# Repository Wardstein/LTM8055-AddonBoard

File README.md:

# LTM8055 Addon Board

This is a small 4 layer addon board with an [LTM8055(-1) DCDC regulator](https://www.analog.com/en/products/ltm8055.html), featuring an INA138 for output current measurement (as the internal current monitor output of the LTM8055 is not very accurate). Additionally a lot of the LTM8055 configuration pins are broken out to a header to be used on the base-board. But this small addon board can also be used as a standalone board, just fit the voltage feedback resistors on this board.

The LTM8055 is a 5-36V input, 8,5A Buck-Boost μModule Regulator with step-up and -down capability from 1,2V to 36V output.

Why use an addon board? This was developed, as the LTM8055 µModules are BGA parts, which are not the easiest parts for home use and soldering. This module can be very easily be soldered on a hotplate (I use the Miniware MHP30).

This board is for example used in the [joseng.de Lab-Box project](https://github.com/Wardstein/Lab-Box) in the multi-power-supply module. 

# License
The content of this whole repository is licensed under [CERN-OHL-W v2](License/cern_ohl_w_v2.txt) or later by Jonas Eberhard.

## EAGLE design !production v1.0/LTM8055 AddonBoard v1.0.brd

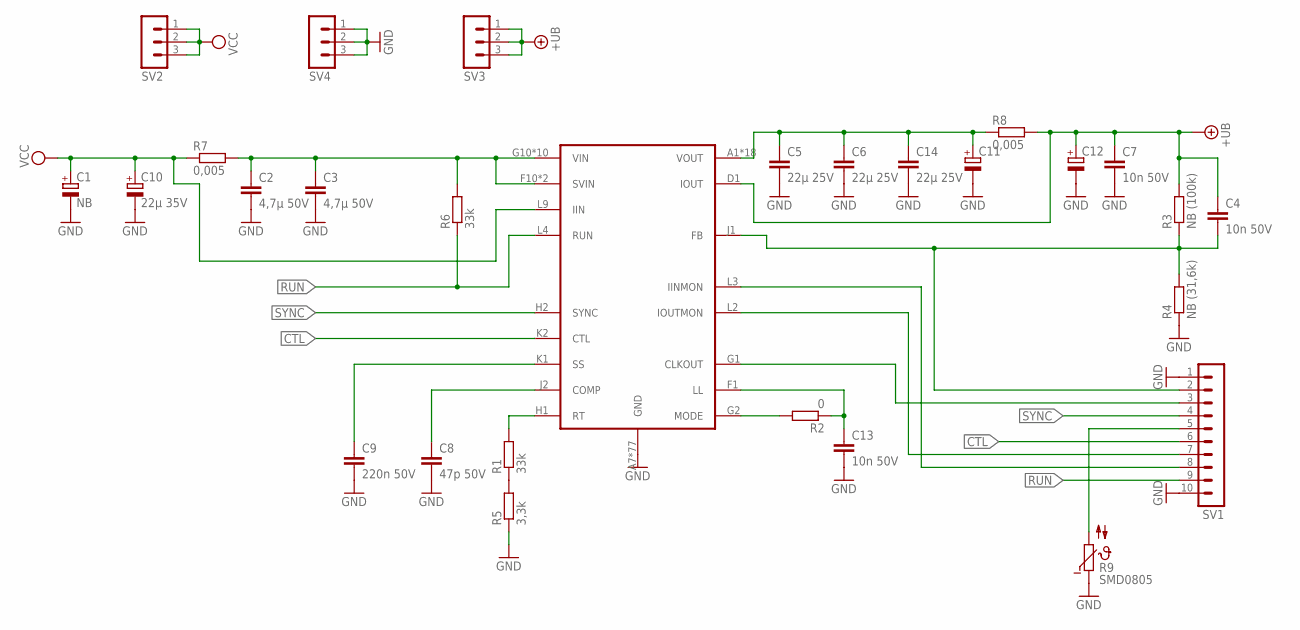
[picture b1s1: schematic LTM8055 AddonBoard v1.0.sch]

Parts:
C1: NB; PANASONIC_E
C2, C3: 4,7µ 50V; C1206
C4, C7, C13: 10n 50V; C0805
C5, C6, C14: 22µ 25V; C1210
C8: 47p 50V; C0805
C9: 220n 50V; C0805
C10: 22µ 35V; D/7343-31R
C11, C12: CPOL-EUD/7343-31R; D/7343-31R
IC1: LTM8055-1; BGA121_1.27_15X15MM
R1, R6: 33k; R0805
R2: 0; R0805
R3: NB (100k); R0805
R4: NB (31,6k); R0805
R5: 3,3k; R0805
R7, R8: 0,005; R2512
R9: SMD0805; R0805
SV1: MA10-1
SV2, SV3, SV4: MA03-1

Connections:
+UB: C4.1, C7.1, C12.+, IC1.D1 (IOUT), R3.2, R8.2, SV3.1, SV3.2, SV3.3
CTL: IC1.K2 (CTL), SV1.6
GND: C1.-, C2.2, C3.2, C5.2, C6.2, C7.2, C8.2, C9.2, C10.-, C11.-, C12.-, C13.2, C14.2, IC1.A7 (GND), IC1.A8 (GND), IC1.A9 (GND), IC1.A10 (GND), IC1.A11 (GND), IC1.B7 (GND), IC1.B8 (GND), IC1.B9 (GND), IC1.B10 (GND), IC1.B11 (GND), IC1.C7 (GND), IC1.C8 (GND), IC1.C9 (GND), IC1.C10 (GND), IC1.C11 (GND), IC1.D2 (GND), IC1.D3 (GND), IC1.D4 (GND), IC1.D5 (GND), IC1.D6 (GND), IC1.D7 (GND), IC1.D8 (GND), IC1.D9 (GND), IC1.D10 (GND), IC1.D11 (GND), IC1.E1 (GND), IC1.E2 (GND), IC1.E3 (GND), IC1.E4 (GND), IC1.E5 (GND), IC1.E6 (GND), IC1.E7 (GND), IC1.E8 (GND), IC1.E9 (GND), IC1.E10 (GND), IC1.E11 (GND), IC1.F2 (GND), IC1.F3 (GND), IC1.F4 (GND), IC1.F5 (GND), IC1.F6 (GND), IC1.F7 (GND), IC1.F8 (GND), IC1.F9 (GND), IC1.G3 (GND), IC1.G4 (GND), IC1.G5 (GND), IC1.G6 (GND), IC1.G7 (GND), IC1.G8 (GND), IC1.G9 (GND), IC1.H3 (GND), IC1.H4 (GND), IC1.H5 (GND), IC1.H6 (GND), IC1.H7 (GND), IC1.H8 (GND), IC1.H9 (GND), IC1.J3 (GND), IC1.J4 (GND), IC1.J5 (GND), IC1.J6 (GND), IC1.J7 (GND), IC1.J8 (GND), IC1.J9 (GND), IC1.K3 (GND), IC1.K4 (GND), IC1.K5 (GND), IC1.K6 (GND), IC1.K7 (GND), IC1.K8 (GND), IC1.K9 (GND), IC1.L1 (GND), IC1.L5 (GND), IC1.L6 (GND), IC1.L7 (GND), IC1.L8 (GND), R4.1, R5.1, R9.1, SV1.1, SV1.10, SV4.1, SV4.2, SV4.3
unnamed: C13.1, IC1.F1 (LL), R2.1
unnamed: IC1.G2 (MODE), R2.2
unnamed: IC1.G1 (CLKOUT), SV1.3
unnamed: C9.1, IC1.K1 (SS)
unnamed: C4.2, IC1.J1 (FB), R3.1, R4.2, SV1.2
unnamed: IC1.L2 (IOUTMON), SV1.7
unnamed: IC1.L3 (IINMON), SV1.8
unnamed: IC1.H1 (RT), R1.2
unnamed: C2.1, C3.1, IC1.F10 (SVIN), IC1.F11 (SVIN), IC1.G10 (VIN), IC1.G11 (VIN), IC1.H10 (VIN), IC1.H11 (VIN), IC1.J10 (VIN), IC1.J11 (VIN), IC1.K10 (VIN), IC1.K11 (VIN), IC1.L10 (VIN), IC1.L11 (VIN), R6.2, R7.2
unnamed: R1.1, R5.2
unnamed: C8.1, IC1.J2 (COMP)
unnamed: R9.2, SV1.5
unnamed: C5.1, C6.1, C11.+, C14.1, IC1.A1 (VOUT), IC1.A2 (VOUT), IC1.A3 (VOUT), IC1.A4 (VOUT), IC1.A5 (VOUT), IC1.A6 (VOUT), IC1.B1 (VOUT), IC1.B2 (VOUT), IC1.B3 (VOUT), IC1.B4 (VOUT), IC1.B5 (VOUT), IC1.B6 (VOUT), IC1.C1 (VOUT), IC1.C2 (VOUT), IC1.C3 (VOUT), IC1.C4 (VOUT), IC1.C5 (VOUT), IC1.C6 (VOUT), R8.1
RUN: IC1.L4 (RUN), R6.1, SV1.9
SYNC: IC1.H2 (SYNC), SV1.4
VCC: C1.+, C10.+, IC1.L9 (IIN), R7.1, SV2.1, SV2.2, SV2.3

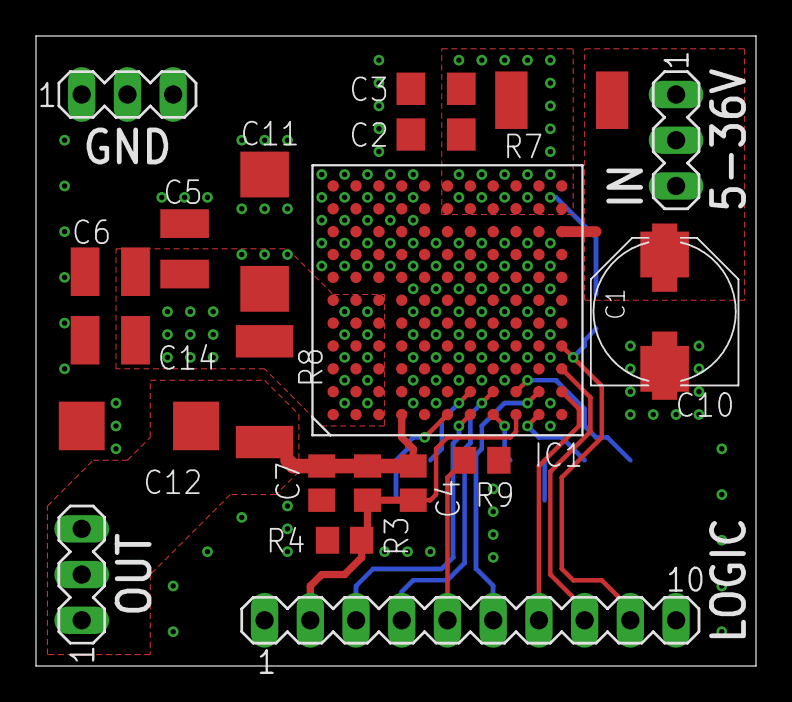
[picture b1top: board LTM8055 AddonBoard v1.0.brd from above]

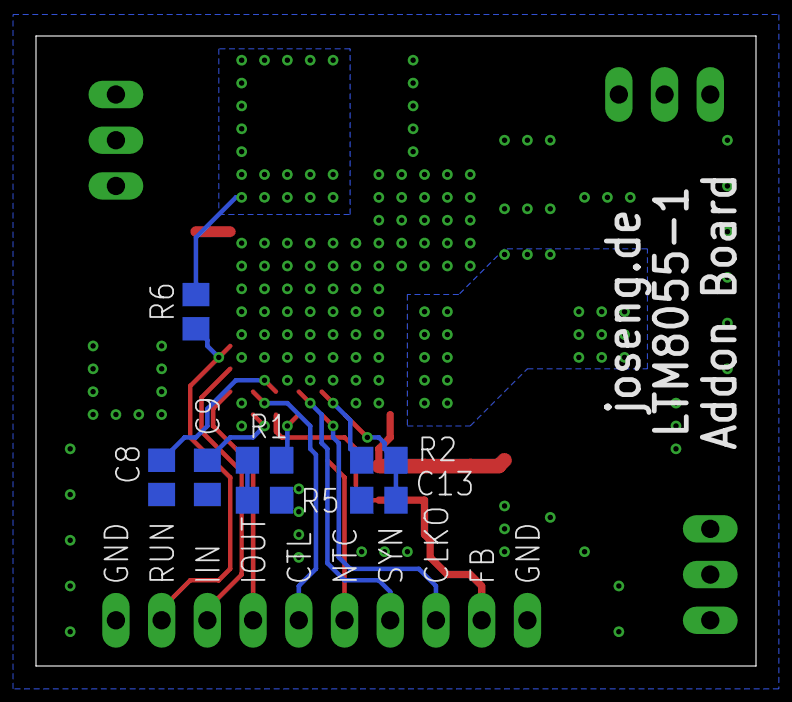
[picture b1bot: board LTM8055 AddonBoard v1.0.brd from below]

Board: 4 copper layers, 40.0 x 35.0 mm, 28 parts (7 on the bottom side), 19 nets.

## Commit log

2023-12-23 Adding all files
